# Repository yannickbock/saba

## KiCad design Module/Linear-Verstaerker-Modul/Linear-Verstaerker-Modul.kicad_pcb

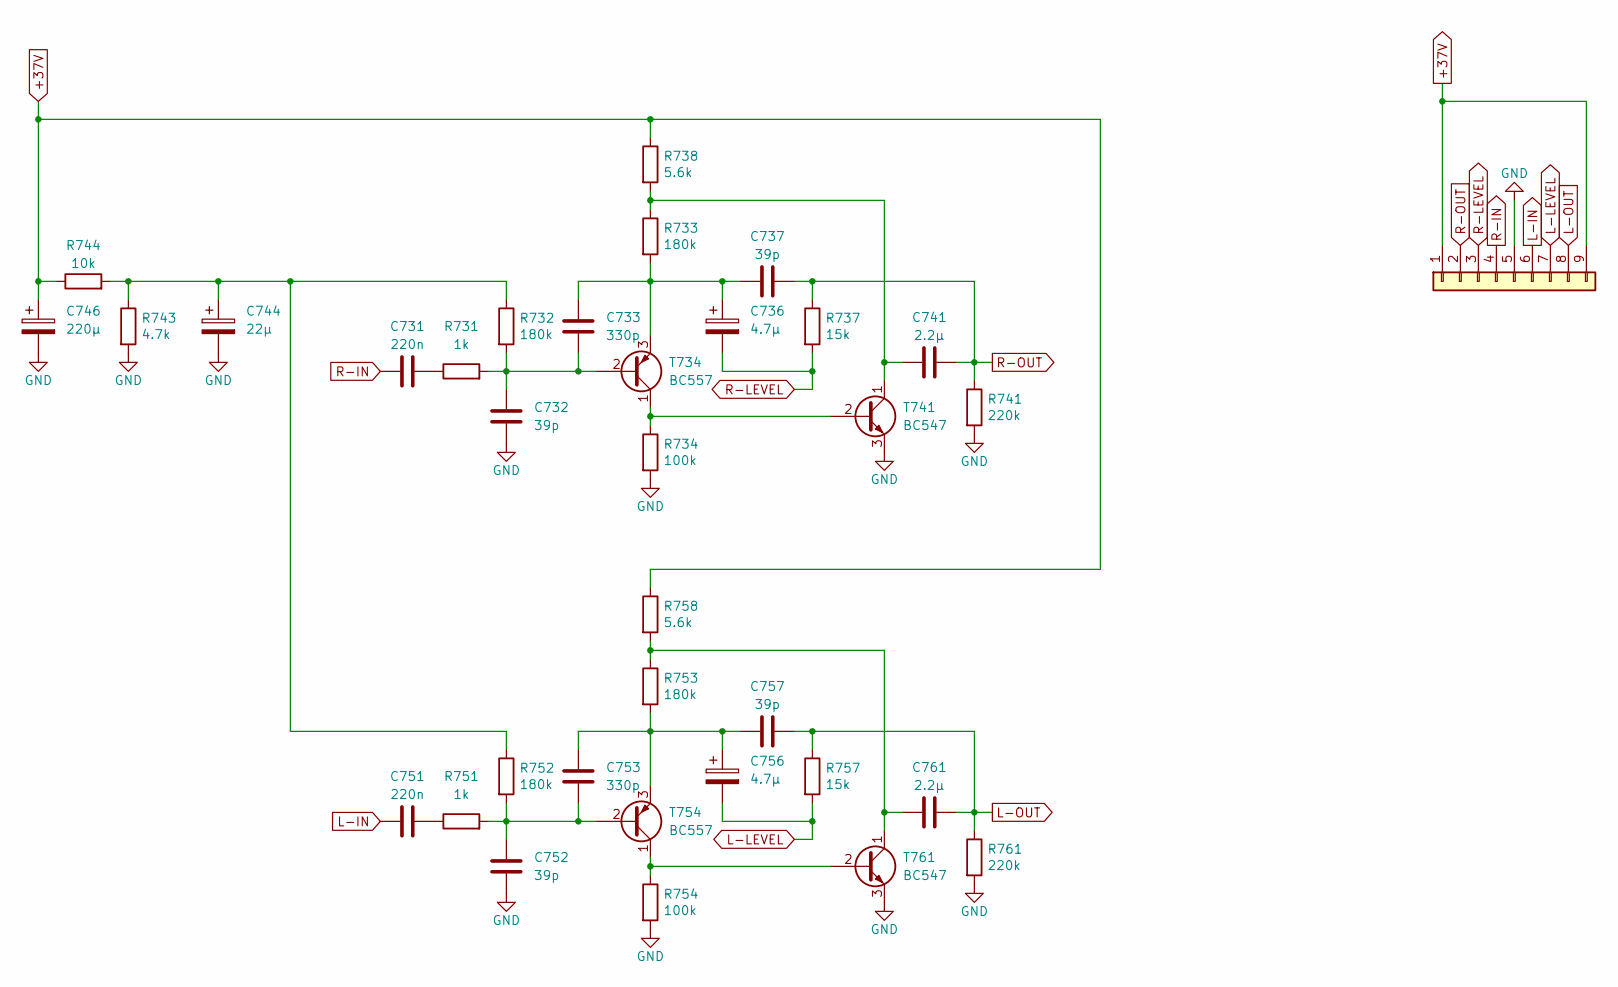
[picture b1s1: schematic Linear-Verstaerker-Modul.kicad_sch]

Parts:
C731, C751: 220n; C_Rect_L10.3mm_W5.0mm_P7.50mm_MKS4
C732, C737, C752, C757: 39p; C_Disc_D4.3mm_W1.9mm_P5.00mm
C733, C753: 330p; C_Disc_D4.3mm_W1.9mm_P5.00mm
C736, C756: 4.7µ; CP_Radial_D5.0mm_P2.00mm
C741, C761: 2.2µ; C_Rect_L7.2mm_W7.2mm_P5.00mm_FKS2_FKP2_MKS2_MKP2
C744: 22µ; CP_Radial_D5.0mm_P2.00mm
C746: 220µ; CP_Radial_D10.0mm_P5.00mm
J1: Conn_01x09; Connector_01x09_5mm
R731, R751: 1k; R_Axial_DIN0207_L6.3mm_D2.5mm_P10.16mm_Horizontal
R732, R733, R752, R753: 180k; R_Axial_DIN0207_L6.3mm_D2.5mm_P10.16mm_Horizontal
R734, R754: 100k; R_Axial_DIN0207_L6.3mm_D2.5mm_P10.16mm_Horizontal
R737, R757: 15k; R_Axial_DIN0207_L6.3mm_D2.5mm_P10.16mm_Horizontal
R738, R758: 5.6k; R_Axial_DIN0207_L6.3mm_D2.5mm_P10.16mm_Horizontal
R741, R761: 220k; R_Axial_DIN0207_L6.3mm_D2.5mm_P10.16mm_Horizontal
R743: 4.7k; R_Axial_DIN0207_L6.3mm_D2.5mm_P10.16mm_Horizontal
R744: 10k; R_Axial_DIN0207_L6.3mm_D2.5mm_P10.16mm_Horizontal
T734, T754: BC557; TO-92L_Wide
T741, T761: BC547; TO-92L_Wide

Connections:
+37V: C746.1, J1.1, J1.9, R738.1, R744.1, R758.1
GND: C732.2, C744.2, C746.2, C752.2, J1.5, R734.2, R741.2, R743.2, R754.2, R761.2, T741.3 (E), T761.3 (E)
L-IN: C751.1, J1.6
L-LEVEL: C756.2, J1.7, R757.2
L-OUT: C757.2, C761.2, J1.8, R757.1, R761.1
unnamed: C731.2, R731.1
unnamed: C744.1, R732.1, R743.1, R744.2, R752.1
unnamed: C751.2, R751.1
unnamed: C732.1, C733.1, R731.2, R732.2, T734.2 (B)
unnamed: R734.1, T734.1 (C), T741.2 (B)
unnamed: C733.2, C736.1, C737.1, R733.2, T734.3 (E)
unnamed: C741.1, R733.1, R738.2, T741.1 (C)
unnamed: C752.1, C753.1, R751.2, R752.2, T754.2 (B)
unnamed: R754.1, T754.1 (C), T761.2 (B)
unnamed: C753.2, C756.1, C757.1, R753.2, T754.3 (E)
unnamed: C761.1, R753.1, R758.2, T761.1 (C)
R-IN: C731.1, J1.4
R-LEVEL: C736.2, J1.3, R737.2
R-OUT: C737.2, C741.2, J1.2, R737.1, R741.1

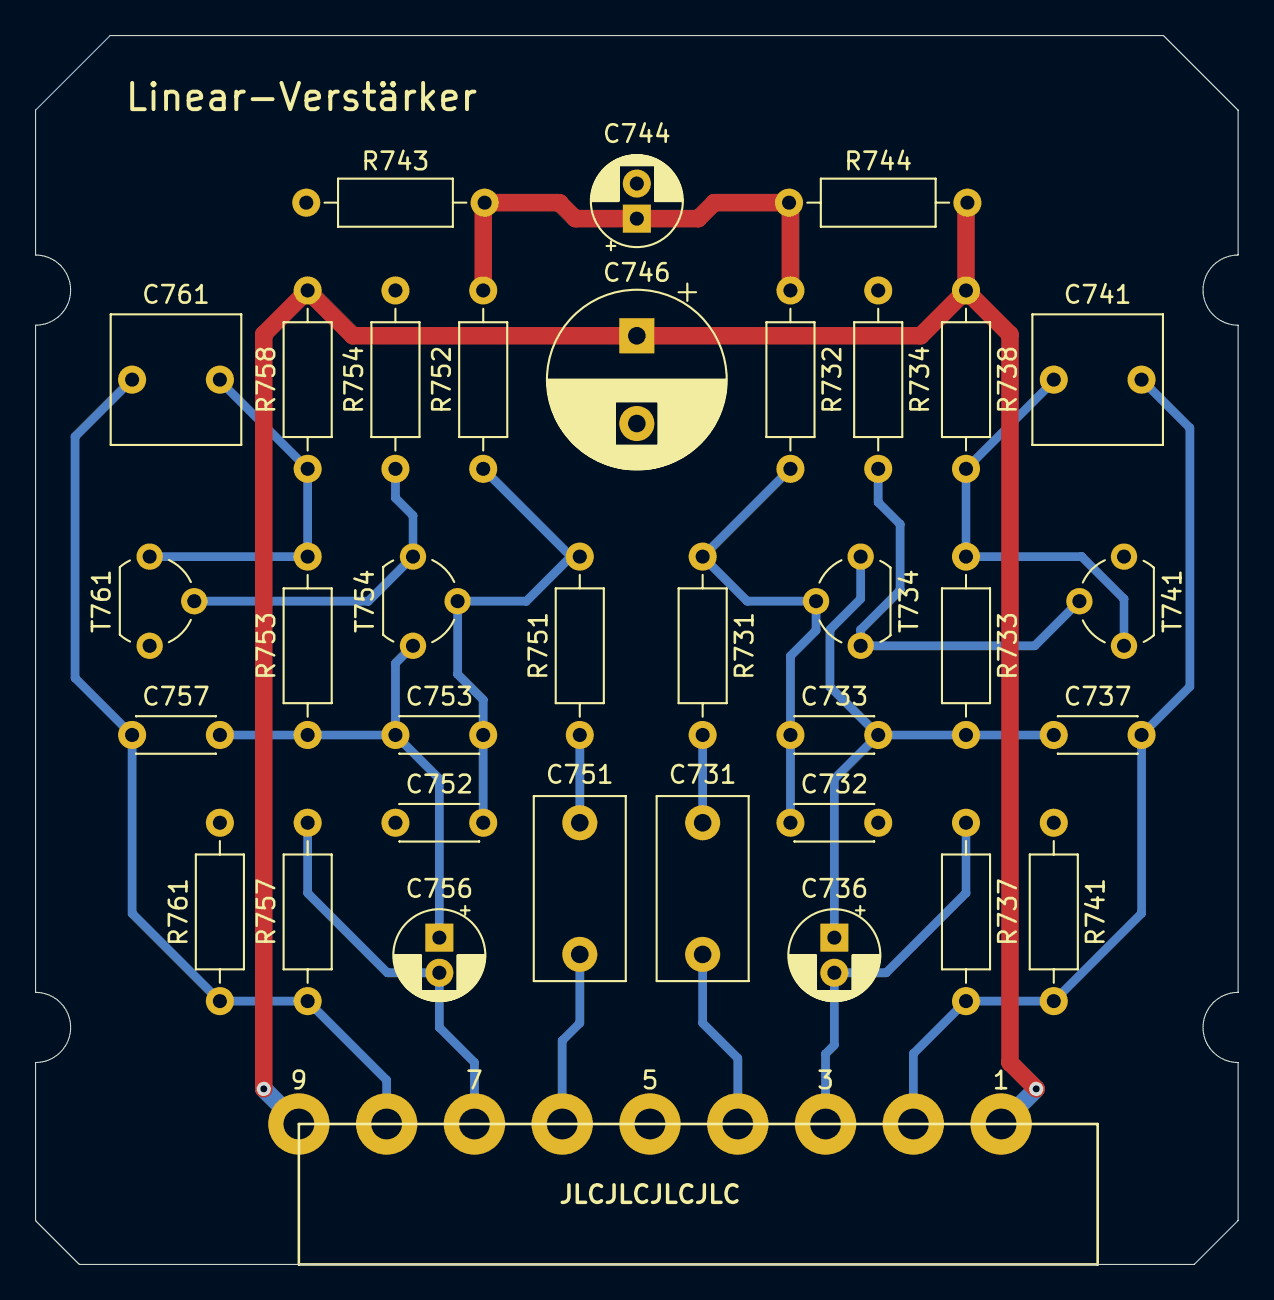
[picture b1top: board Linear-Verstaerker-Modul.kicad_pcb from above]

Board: 2 copper layers, 68.5 x 70.0 mm, 35 parts (0 on the bottom side), 19 nets.

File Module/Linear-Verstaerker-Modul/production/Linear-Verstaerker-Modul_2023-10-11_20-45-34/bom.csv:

Designator,Footprint,Quantity,Value,LCSC Part #
"C731, C751",C_Rect_L10.3mm_W5.0mm_P7.50mm_MKS4,2,220n,
"C732, C737, C752, C757",C_Disc_D4.3mm_W1.9mm_P5.00mm,4,39p,
"C733, C753",C_Disc_D4.3mm_W1.9mm_P5.00mm,2,330p,
"C736, C756",CP_Radial_D5.0mm_P2.00mm,2,4.7µ,
"C741, C761",C_Rect_L7.2mm_W7.2mm_P5.00mm_FKS2_FKP2_MKS2_MKP2,2,2.2µ,
C744,CP_Radial_D5.0mm_P2.00mm,1,22µ,
C746,CP_Radial_D10.0mm_P5.00mm,1,220µ,
J1,Connector_01x09_5mm,1,Conn_01x09,
"R731, R751",R_Axial_DIN0207_L6.3mm_D2.5mm_P10.16mm_Horizontal,2,1k,
"R732, R733, R752, R753",R_Axial_DIN0207_L6.3mm_D2.5mm_P10.16mm_Horizontal,4,180k,
"R734, R754",R_Axial_DIN0207_L6.3mm_D2.5mm_P10.16mm_Horizontal,2,100k,
"R737, R757",R_Axial_DIN0207_L6.3mm_D2.5mm_P10.16mm_Horizontal,2,15k,
"R738, R758",R_Axial_DIN0207_L6.3mm_D2.5mm_P10.16mm_Horizontal,2,5.6k,
"R741, R761",R_Axial_DIN0207_L6.3mm_D2.5mm_P10.16mm_Horizontal,2,220k,
R743,R_Axial_DIN0207_L6.3mm_D2.5mm_P10.16mm_Horizontal,1,4.7k,
R744,R_Axial_DIN0207_L6.3mm_D2.5mm_P10.16mm_Horizontal,1,10k,
"T734, T754",TO-92L_Wide,2,BC557,
"T741, T761",TO-92L_Wide,2,BC547,

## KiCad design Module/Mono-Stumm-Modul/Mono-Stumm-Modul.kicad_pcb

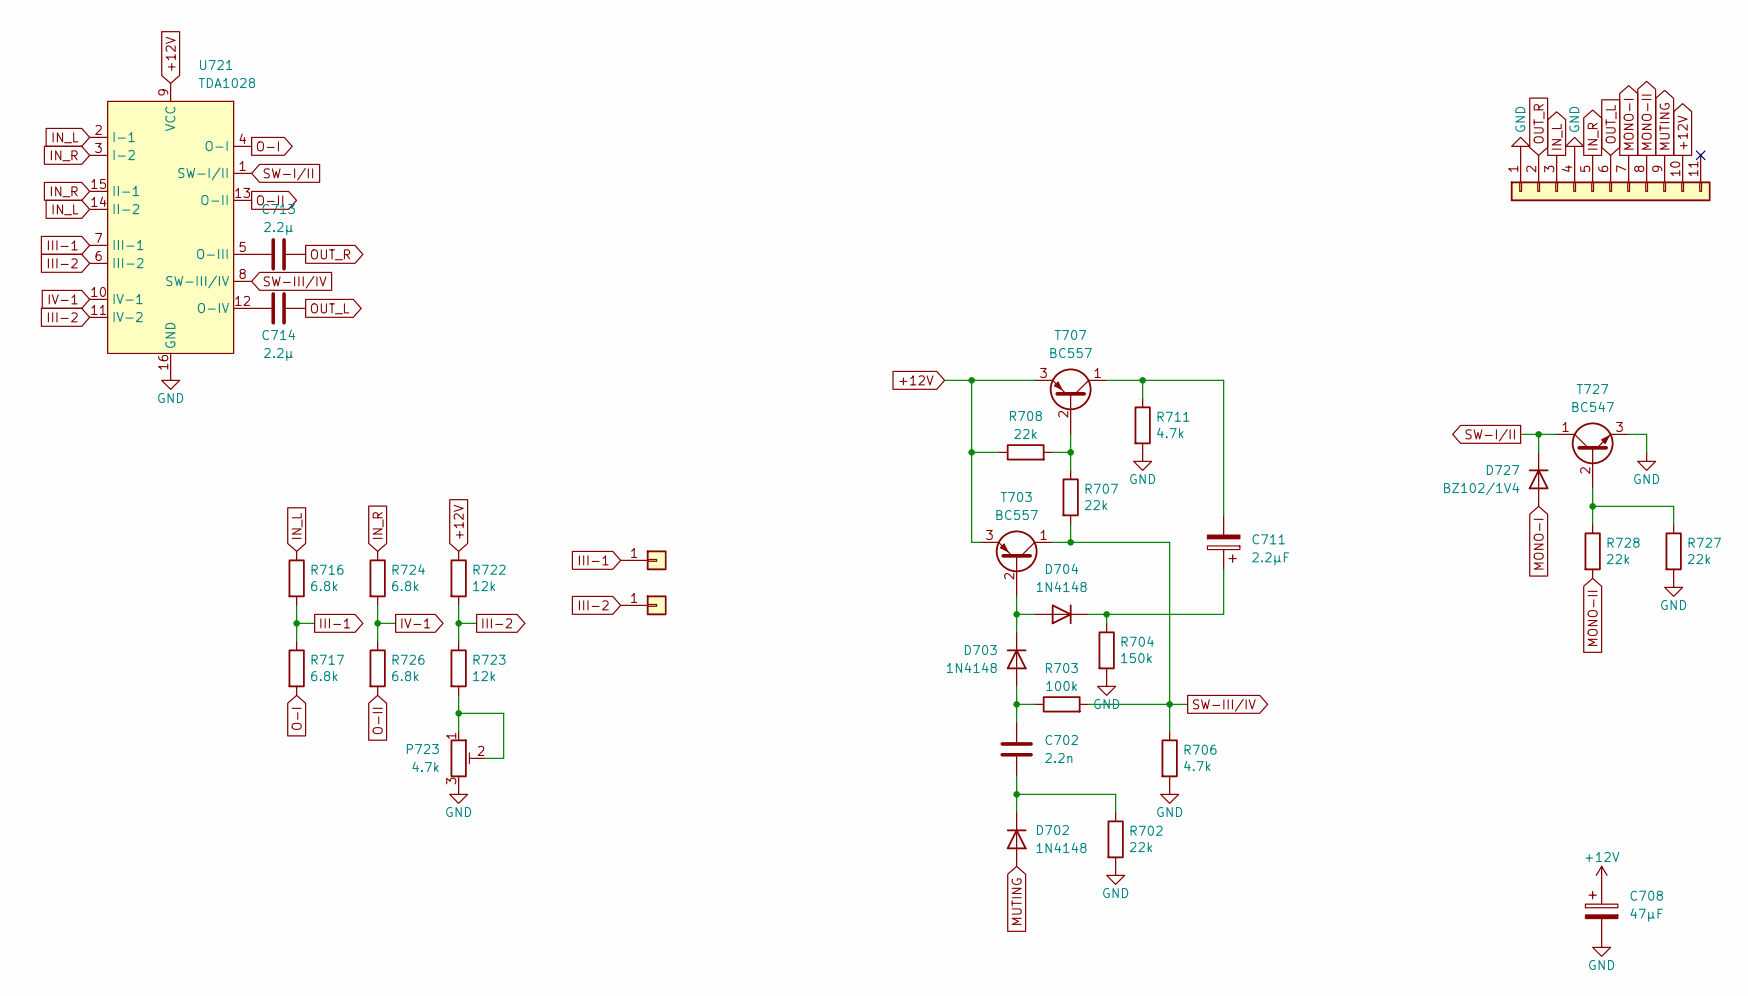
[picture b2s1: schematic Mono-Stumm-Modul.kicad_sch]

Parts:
C702: 2.2n; C_Rect_L10.0mm_W2.5mm_P7.50mm_MKS4
C708: 47µF; CP_Radial_D6.3mm_P2.50mm
C711: 2.2µF; CP_Radial_D5.0mm_P2.00mm
C713, C714: 2.2µ; C_Rect_L7.2mm_W7.2mm_P5.00mm_FKS2_FKP2_MKS2_MKP2
D702, D703, D704: 1N4148; D_DO-35_SOD27_P10.16mm_Horizontal
D727: BZ102/1V4; D_DO-35_SOD27_P10.16mm_Horizontal
J1: Conn_01x13; Connector_01x11_5mm
J2, J3: Conn_01x01; TestPoint_Loop_D1.80mm_Drill1.0mm_Beaded
P723: 4.7k; Potentiometer_Piher_PT-10-H01_Horizontal
R702, R707, R708, R727, R728: 22k; R_Axial_DIN0207_L6.3mm_D2.5mm_P10.16mm_Horizontal
R703: 100k; R_Axial_DIN0207_L6.3mm_D2.5mm_P10.16mm_Horizontal
R704: 150k; R_Axial_DIN0207_L6.3mm_D2.5mm_P10.16mm_Horizontal
R706, R711: 4.7k; R_Axial_DIN0207_L6.3mm_D2.5mm_P10.16mm_Horizontal
R716, R717, R724, R726: 6.8k; R_Axial_DIN0207_L6.3mm_D2.5mm_P10.16mm_Horizontal
R722, R723: 12k; R_Axial_DIN0207_L6.3mm_D2.5mm_P10.16mm_Horizontal
T703, T707: BC557; TO-92_Wide
T727: BC547; TO-92_Wide
U721: TDA1028; DIP-16_W7.62mm

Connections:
+12V: C708.1, J1.10, R708.1, R722.1, T703.3 (E), T707.3 (E), U721.9 (VCC)
GND: C708.2, J1.1, J1.4, P723.3, R702.2, R704.2, R706.2, R711.2, R727.2, T727.3 (E), U721.16 (GND)
III-1: J2.1, R716.2, R717.1, U721.7 (III-1)
III-2: J3.1, R722.2, R723.1, U721.6 (III-2), U721.11 (IV-2)
IN_L: J1.3, R716.1, U721.2 (I-1), U721.14 (II-2)
IN_R: J1.5, R724.1, U721.3 (I-2), U721.15 (II-1)
IV-1: R724.2, R726.1, U721.10 (IV-1)
MONO-I: D727.2 (A), J1.7
MONO-II: J1.8, R728.2
MUTING: D702.2 (A), J1.9
unnamed: C702.2, D702.1 (K), R702.1
unnamed: C702.1, D703.2 (A), R703.1
unnamed: D703.1 (K), D704.2 (A), T703.2 (B)
unnamed: C711.1, D704.1 (K), R704.1
unnamed: P723.1, P723.2, R723.2
unnamed: R707.1, R708.2, T707.2 (B)
unnamed: C711.2, R711.1, T707.1 (C)
unnamed: R727.1, R728.1, T727.2 (B)
unnamed: C713.1, U721.5 (O-III)
unnamed: C714.1, U721.12 (O-IV)
O-I: R717.2, U721.4 (O-I)
O-II: R726.2, U721.13 (O-II)
OUT_L: C714.2, J1.6
OUT_R: C713.2, J1.2
SW-III/IV: R703.2, R706.1, R707.2, T703.1 (C), U721.8 (SW-III/IV)
SW-I/II: D727.1 (K), T727.1 (C), U721.1 (SW-I/II)

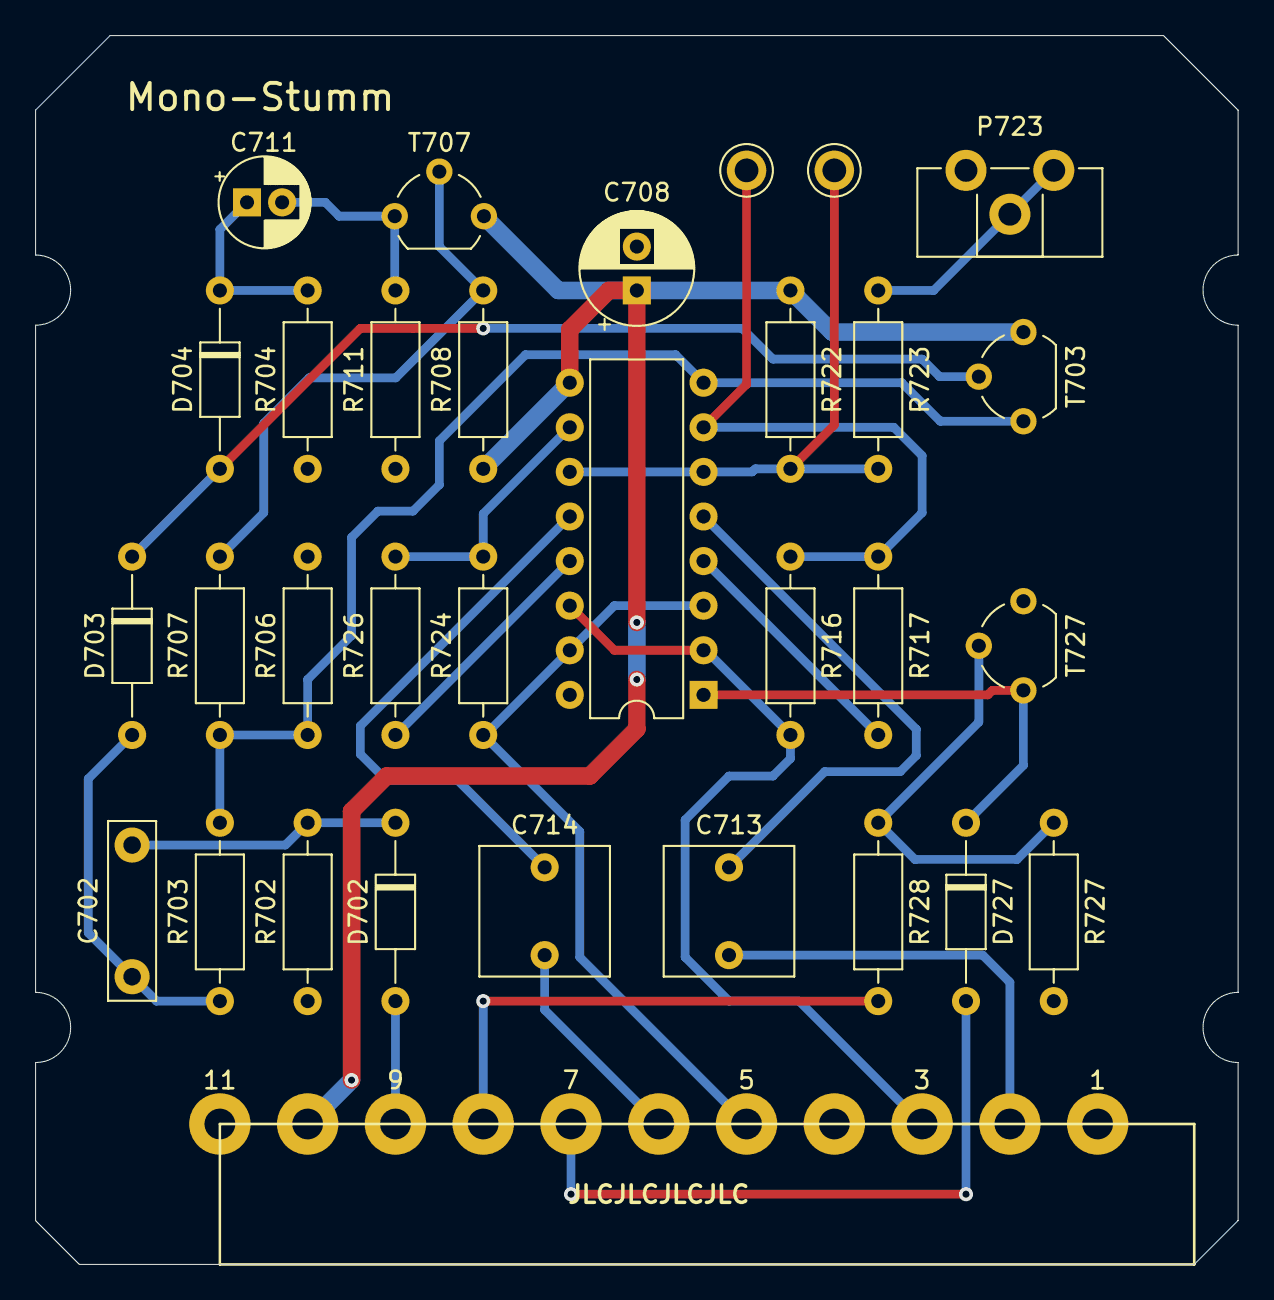
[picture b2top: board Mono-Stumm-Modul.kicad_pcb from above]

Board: 2 copper layers, 68.5 x 70.0 mm, 32 parts (0 on the bottom side), 26 nets.

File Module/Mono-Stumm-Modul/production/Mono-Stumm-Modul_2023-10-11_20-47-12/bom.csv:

Designator,Footprint,Quantity,Value,LCSC Part #
C702,C_Rect_L10.0mm_W2.5mm_P7.50mm_MKS4,1,2.2n,
C708,CP_Radial_D6.3mm_P2.50mm,1,47µF,
C711,CP_Radial_D5.0mm_P2.00mm,1,2.2µF,
"C713, C714",C_Rect_L7.2mm_W7.2mm_P5.00mm_FKS2_FKP2_MKS2_MKP2,2,2.2µ,
"D702, D703, D704",D_DO-35_SOD27_P10.16mm_Horizontal,3,1N4148,
D727,D_DO-35_SOD27_P10.16mm_Horizontal,1,BZ102/1V4,
J1,Connector_01x11_5mm,1,Conn_01x13,
"J2, J3",TestPoint_Loop_D1.80mm_Drill1.0mm_Beaded,2,Conn_01x01,
P723,Potentiometer_Piher_PT-10-H01_Horizontal,1,4.7k,
"R702, R707, R708, R727, R728",R_Axial_DIN0207_L6.3mm_D2.5mm_P10.16mm_Horizontal,5,22k,
R703,R_Axial_DIN0207_L6.3mm_D2.5mm_P10.16mm_Horizontal,1,100k,
R704,R_Axial_DIN0207_L6.3mm_D2.5mm_P10.16mm_Horizontal,1,150k,
"R706, R711",R_Axial_DIN0207_L6.3mm_D2.5mm_P10.16mm_Horizontal,2,4.7k,
"R716, R717, R724, R726",R_Axial_DIN0207_L6.3mm_D2.5mm_P10.16mm_Horizontal,4,6.8k,
R722,R_Axial_DIN0207_L6.3mm_D2.5mm_P10.16mm_Horizontal,1,12k,
R723,R_Axial_DIN0207_L6.3mm_D2.5mm_P10.16mm_Horizontal,1,12k,
"T703, T707",TO-92_Wide,2,BC557,
T727,TO-92_Wide,1,BC547,
U721,DIP-16_W7.62mm,1,TDA1028,

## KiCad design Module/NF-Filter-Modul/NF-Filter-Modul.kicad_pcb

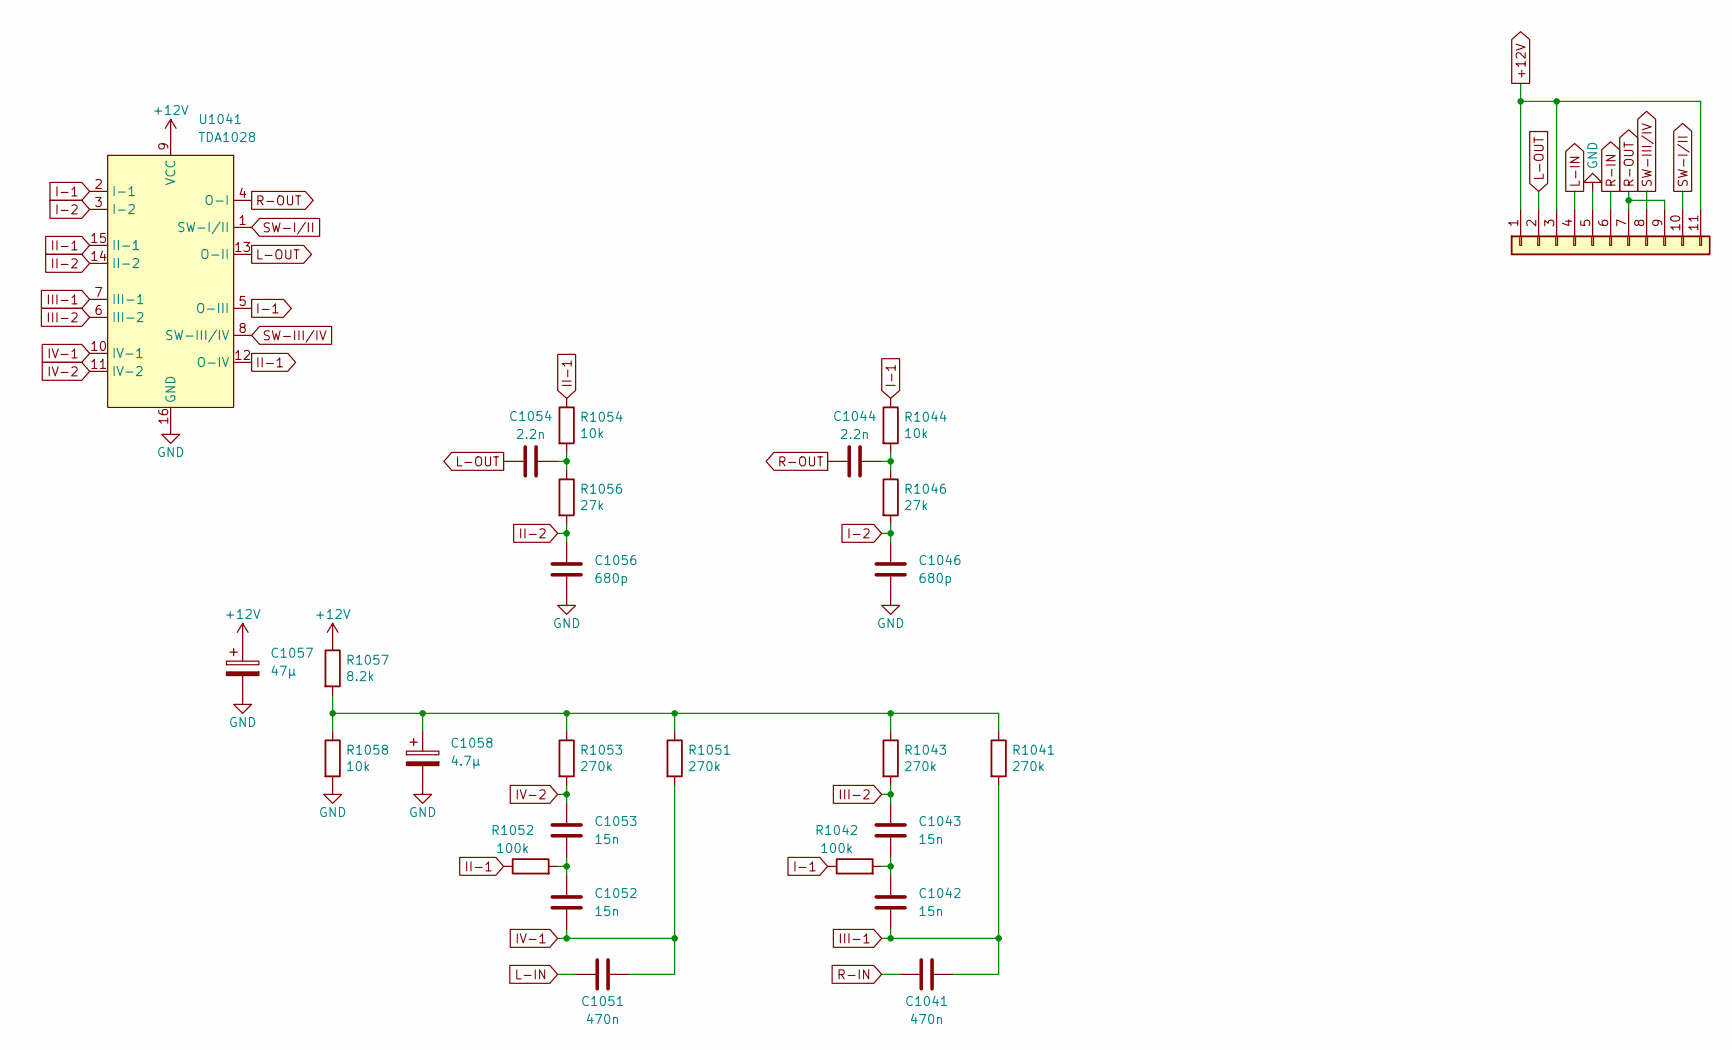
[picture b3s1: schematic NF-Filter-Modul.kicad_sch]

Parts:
C1041, C1051: 470n; C_Rect_L10.0mm_W4.0mm_P7.50mm_MKS4
C1042, C1043, C1052, C1053: 15n; C_Rect_L10.0mm_W2.5mm_P7.50mm_MKS4
C1044, C1054: 2.2n; C_RAD_6.5mm_5mm
C1046, C1056: 680p; C_RAD_6.5mm_5mm
C1057: 47µ; CP_Radial_D6.3mm_P2.50mm
C1058: 4.7µ; CP_Radial_D5.0mm_P2.00mm
J1: Conn_01x13; Connector_01x11_5mm
R1041, R1043, R1051, R1053: 270k; R_Axial_DIN0207_L6.3mm_D2.5mm_P10.16mm_Horizontal
R1042, R1052: 100k; R_Axial_DIN0207_L6.3mm_D2.5mm_P10.16mm_Horizontal
R1044, R1054, R1058: 10k; R_Axial_DIN0207_L6.3mm_D2.5mm_P10.16mm_Horizontal
R1046, R1056: 27k; R_Axial_DIN0207_L6.3mm_D2.5mm_P10.16mm_Horizontal
R1057: 8.2k; R_Axial_DIN0207_L6.3mm_D2.5mm_P10.16mm_Horizontal
U1041: TDA1028; DIP-16_W7.62mm

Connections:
+12V: C1057.1, J1.1, J1.3, J1.11, R1057.1, U1041.9 (VCC)
GND: C1046.2, C1056.2, C1057.2, C1058.2, J1.5, R1058.2, U1041.16 (GND)
I-1: R1042.1, R1044.1, U1041.2 (I-1), U1041.5 (O-III)
I-2: C1046.1, R1046.2, U1041.3 (I-2)
II-1: R1052.1, R1054.1, U1041.12 (O-IV), U1041.15 (II-1)
II-2: C1056.1, R1056.2, U1041.14 (II-2)
III-1: C1041.1, C1042.2, R1041.2, U1041.7 (III-1)
III-2: C1043.1, R1043.2, U1041.6 (III-2)
IV-1: C1051.1, C1052.2, R1051.2, U1041.10 (IV-1)
IV-2: C1053.1, R1053.2, U1041.11 (IV-2)
L-IN: C1051.2, J1.4
L-OUT: C1054.1, J1.2, U1041.13 (O-II)
unnamed: C1042.1, C1043.2, R1042.2
unnamed: C1044.2, R1044.2, R1046.1
unnamed: C1052.1, C1053.2, R1052.2
unnamed: C1054.2, R1054.2, R1056.1
unnamed: C1058.1, R1041.1, R1043.1, R1051.1, R1053.1, R1057.2, R1058.1
R-IN: C1041.2, J1.6
R-OUT: C1044.1, J1.7, J1.9, U1041.4 (O-I)
SW-III/IV: J1.8, U1041.8 (SW-III/IV)
SW-I/II: J1.10, U1041.1 (SW-I/II)

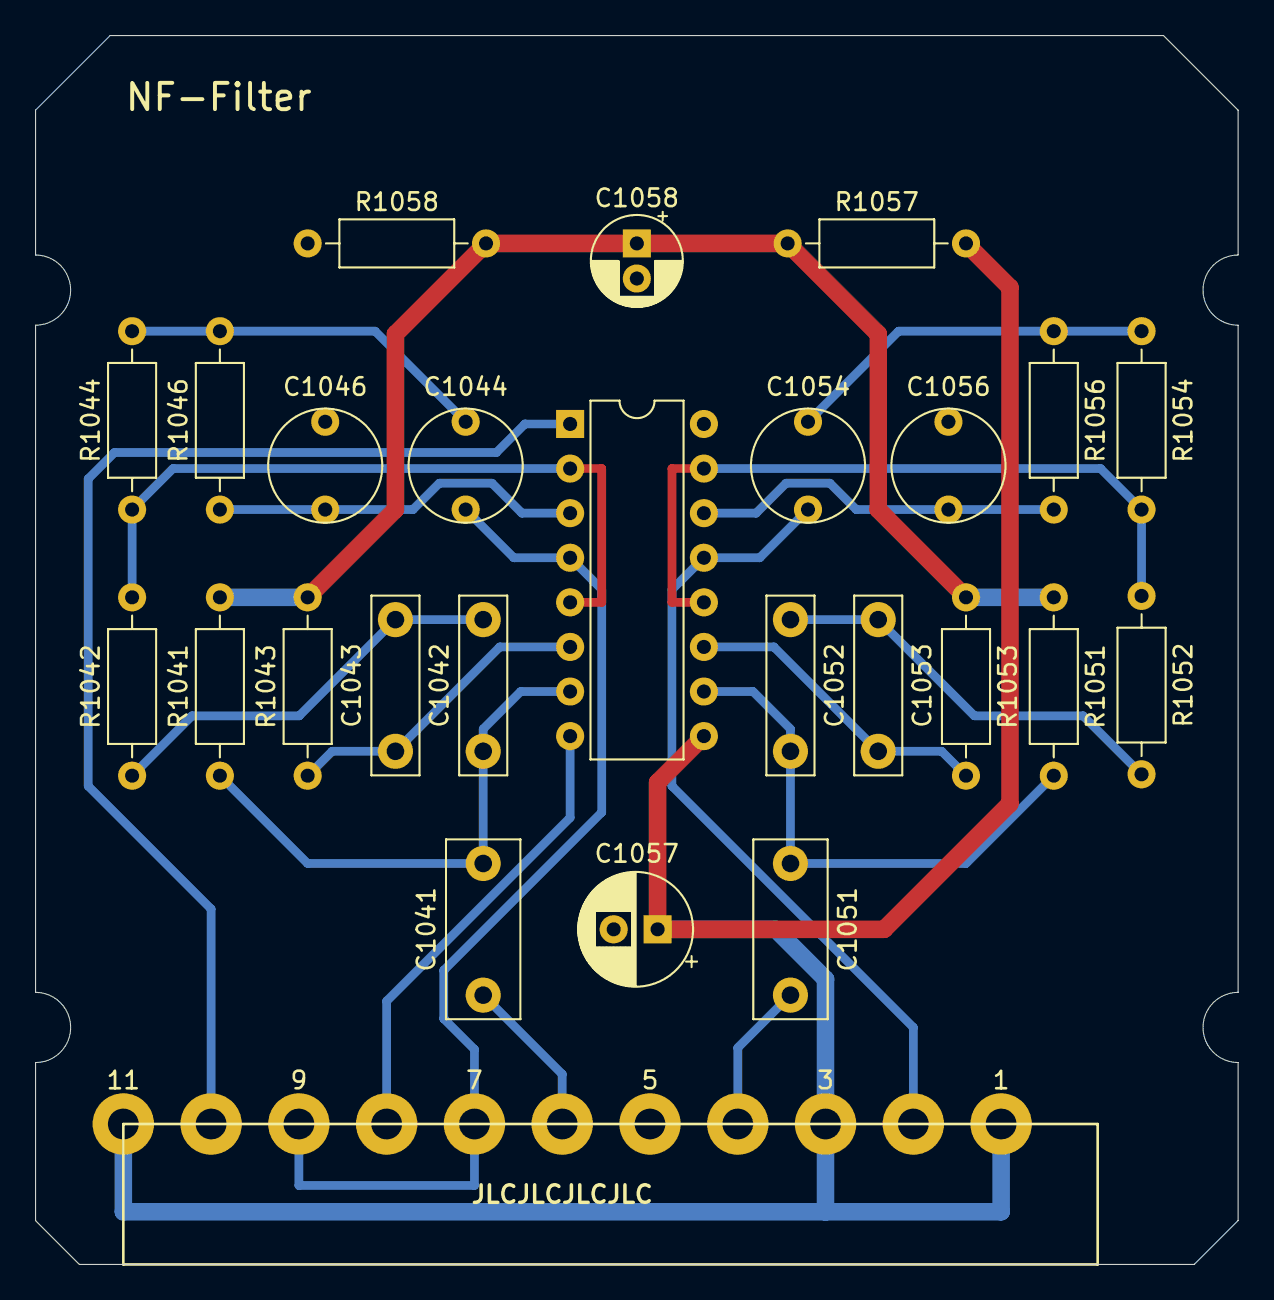
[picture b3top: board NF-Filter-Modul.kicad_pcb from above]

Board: 2 copper layers, 68.5 x 70.0 mm, 26 parts (0 on the bottom side), 21 nets.

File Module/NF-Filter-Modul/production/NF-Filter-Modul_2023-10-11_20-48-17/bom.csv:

Designator,Footprint,Quantity,Value,LCSC Part #
"C1041, C1051",C_Rect_L10.0mm_W4.0mm_P7.50mm_MKS4,2,470n,
"C1042, C1043, C1052, C1053",C_Rect_L10.0mm_W2.5mm_P7.50mm_MKS4,4,15n,
"C1044, C1054",C_RAD_6.5mm_5mm,2,2.2n,
"C1046, C1056",C_RAD_6.5mm_5mm,2,680p,
C1057,CP_Radial_D6.3mm_P2.50mm,1,47µ,
C1058,CP_Radial_D5.0mm_P2.00mm,1,4.7µ,
J1,Connector_01x11_5mm,1,Conn_01x13,
"R1041, R1043, R1051, R1053",R_Axial_DIN0207_L6.3mm_D2.5mm_P10.16mm_Horizontal,4,270k,
"R1042, R1052",R_Axial_DIN0207_L6.3mm_D2.5mm_P10.16mm_Horizontal,2,100k,
"R1044, R1054, R1058",R_Axial_DIN0207_L6.3mm_D2.5mm_P10.16mm_Horizontal,3,10k,
"R1046, R1056",R_Axial_DIN0207_L6.3mm_D2.5mm_P10.16mm_Horizontal,2,27k,
R1057,R_Axial_DIN0207_L6.3mm_D2.5mm_P10.16mm_Horizontal,1,8.2k,
U1041,DIP-16_W7.62mm,1,TDA1028,

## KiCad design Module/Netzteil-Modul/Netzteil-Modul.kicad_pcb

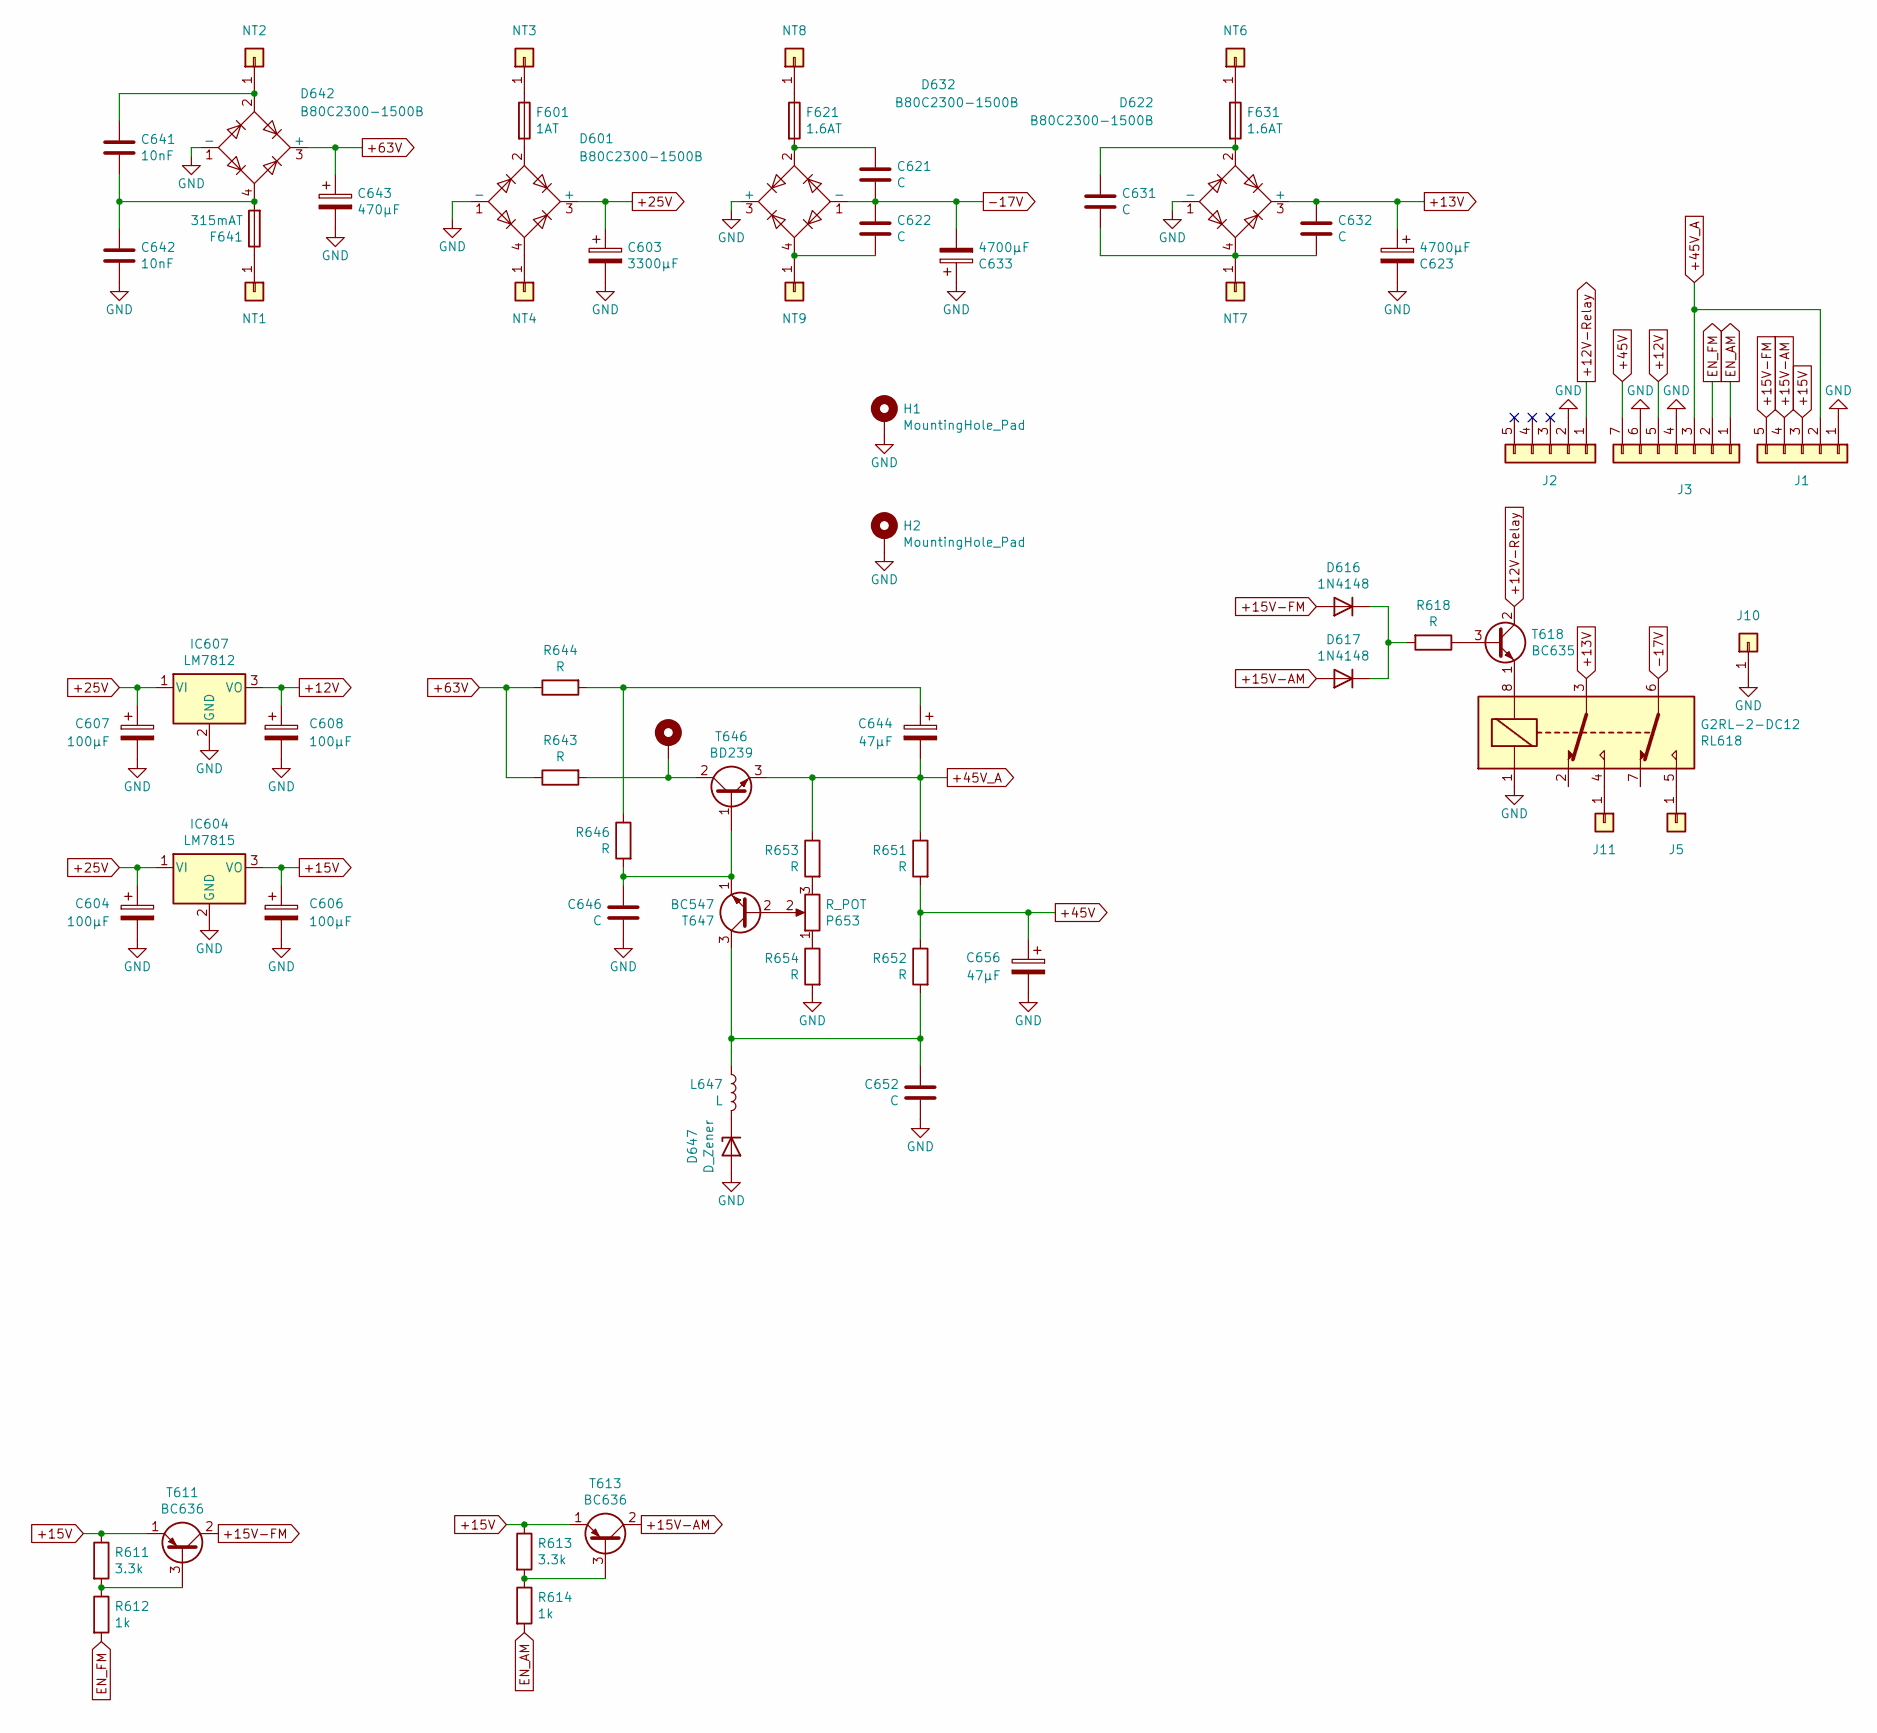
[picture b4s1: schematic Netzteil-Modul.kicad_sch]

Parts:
C603: 3300µF; CP_Radial_D18.0mm_P7.50mm
C604, C606, C607, C608: 100µF; CP_Radial_D8.0mm_P3.50mm
C621, C622, C631, C632: C; C_Rect_L7.2mm_W3.0mm_P5.00mm_FKS2_FKP2_MKS2_MKP2
C623, C633: 4700µF; CP_Radial_D18.0mm_P7.50mm
C641, C642: 10nF; C_Rect_L7.2mm_W2.5mm_P5.00mm_FKS2_FKP2_MKS2_MKP2
C643: 470µF; CP_Radial_D16.0mm_P7.50mm
C644: 47µF; CP_Radial_D6.3mm_P2.50mm
C646, C652: C; C_Rect_L10.0mm_W3.0mm_P7.50mm_MKS4
C656: 47µF; CP_Radial_D8.0mm_P3.50mm
D601, D622, D632, D642: B80C2300-1500B; Diode_Bridge_19.0x3.5x10.0mm_P5.0mm
D616, D617: 1N4148; D_DO-35_SOD27_P5.08mm_Vertical_AnodeUp
D647: D_Zener; D_DO-35_SOD27_P10.16mm_Horizontal
F601: 1AT; Fuseholder5x20_horiz_open_inline_Type-I
F621, F631: 1.6AT; Fuseholder5x20_horiz_open_inline_Type-I
F641: 315mAT; Fuseholder5x20_horiz_open_inline_Type-I
H1, H2, H3: MountingHole_Pad; MountingHole_3.5mm_Pad
IC604: LM7815; TO-220-3_Vertical
IC607: LM7812; TO-220-3_Vertical
J1, J2: Conn_01x05; Connector_01x05_5mm
J3: Conn_01x07; Connector_01x07_5mm
J5, J10, J11: Conn_01x01; SolderWirePad_single_1-2mmDrill
L647: L; L_Axial_L6.6mm_D2.7mm_P10.16mm_Horizontal_Vishay_IM-2
NT1, NT2, NT3, NT4, NT6, NT7, NT8, NT9: Conn_01x01; SolderWirePad_single_1-2mmDrill
P653: R_POT; Potentiometer_Piher_PT-15-H05_Horizontal
R611, R613: 3.3k; R_Axial_DIN0207_L6.3mm_D2.5mm_P5.08mm_Vertical
R612, R614: 1k; R_Axial_DIN0207_L6.3mm_D2.5mm_P10.16mm_Horizontal
R618, R643, R644, R646, R651, R652, R653, R654: R; R_Axial_DIN0207_L6.3mm_D2.5mm_P10.16mm_Horizontal
RL618: G2RL-2-DC12; Relay_DPDTRT2_RM5mm
T611, T613: BC636; TO-92_Wide
T618: BC635; TO-92_Wide
T646: BD239; TO-220-3_Vertical
T647: BC547; TO-92_Wide

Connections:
+12V: C608.1, IC607.3 (VO), J3.5
+12V-Relay: J2.1, T618.2 (C)
+13V: C623.1, C632.2, D622.3 (+), RL618.3
+15V: C606.1, IC604.3 (VO), J1.3, R611.1, R613.1, T611.1 (E), T613.1 (E)
+15V-AM: D617.2 (A), J1.4, T613.2 (C)
+15V-FM: D616.2 (A), J1.5, T611.2 (C)
+25V: C603.1, C604.1, C607.1, D601.3 (+), IC604.1 (VI), IC607.1 (VI)
+45V: C656.1, J3.7, R651.2, R652.1
+45V_A: C644.2, J1.2, J3.3, R651.1, R653.1, T646.3 (E)
+63V: C643.1, D642.3 (+), R643.1, R644.1
-17V: C621.2, C622.1, C633.2, D632.1 (-), RL618.6
EN_AM: J3.1, R614.2
EN_FM: J3.2, R612.2
GND: C603.2, C604.2, C606.2, C607.2, C608.2, C623.2, C633.1, C642.2, C643.2, C646.2, C652.2, C656.2, D601.1 (-), D622.1 (-), D632.3 (+), D642.1 (-), D647.2 (A), H1.1, H2.1, IC604.2 (GND), IC607.2 (GND), J1.1, J2.2, J3.4, J3.6, J10.1, R654.2, RL618.1
unnamed: C621.1, D632.2, F621.2
unnamed: C622.2, D632.4, NT9.1
unnamed: C631.1, D622.2, F631.2
unnamed: C631.2, C632.1, D622.4, NT7.1
unnamed: C641.1, D642.2, NT2.1
unnamed: C641.2, C642.1, D642.4, F641.2
unnamed: C644.1, R644.2, R646.1
unnamed: C646.1, R646.2, T646.1 (B), T647.1 (E)
unnamed: C652.1, L647.2, R652.2, T647.3 (C)
unnamed: D601.2, F601.2
unnamed: D601.4, NT4.1
unnamed: D616.1 (K), D617.1 (K), R618.2
unnamed: D647.1 (K), L647.1
unnamed: F601.1, NT3.1
unnamed: F621.1, NT8.1
unnamed: F631.1, NT6.1
unnamed: F641.1, NT1.1
unnamed: H3.1, R643.2, T646.2 (C)
unnamed: P653.1, R654.1
unnamed: P653.2, T647.2 (B)
unnamed: P653.3, R653.2
unnamed: R611.2, R612.1, T611.3 (B)
unnamed: R613.2, R614.1, T613.3 (B)
unnamed: R618.1, T618.3 (B)
unnamed: J11.1, RL618.4
unnamed: J5.1, RL618.5
unnamed: RL618.8, T618.1 (E)

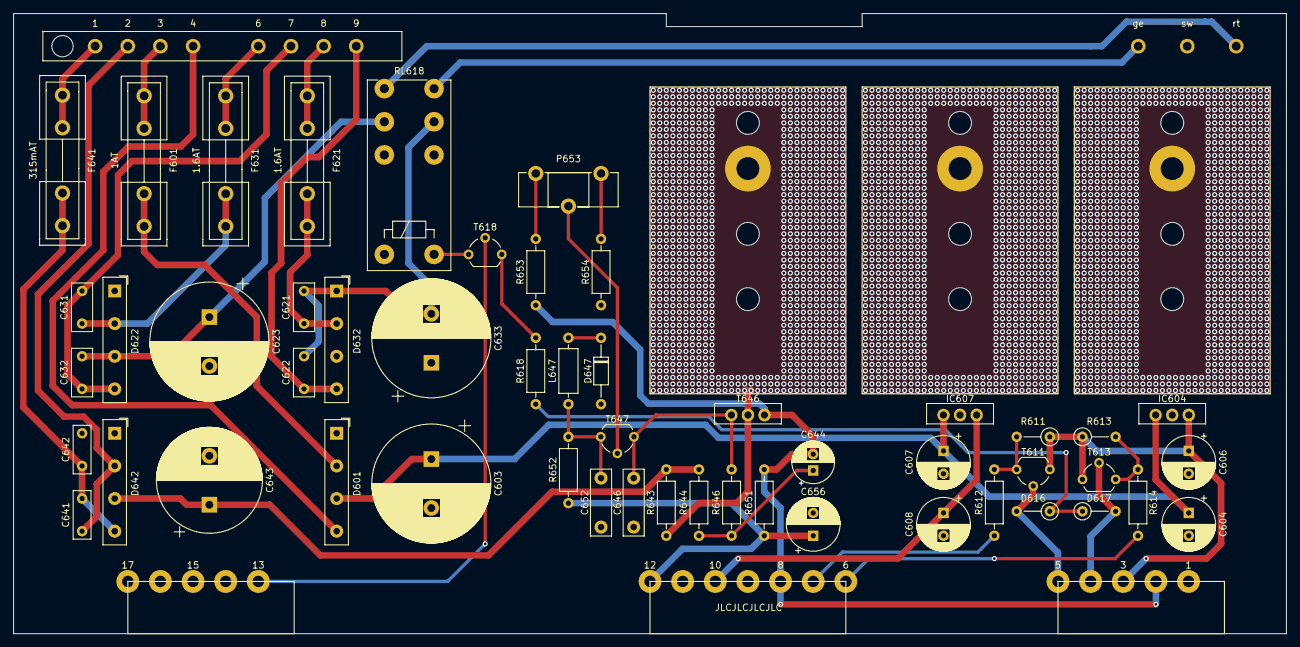
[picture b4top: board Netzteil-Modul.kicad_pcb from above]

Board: 2 copper layers, 195.0 x 95.0 mm, 68 parts (0 on the bottom side), 41 nets.
